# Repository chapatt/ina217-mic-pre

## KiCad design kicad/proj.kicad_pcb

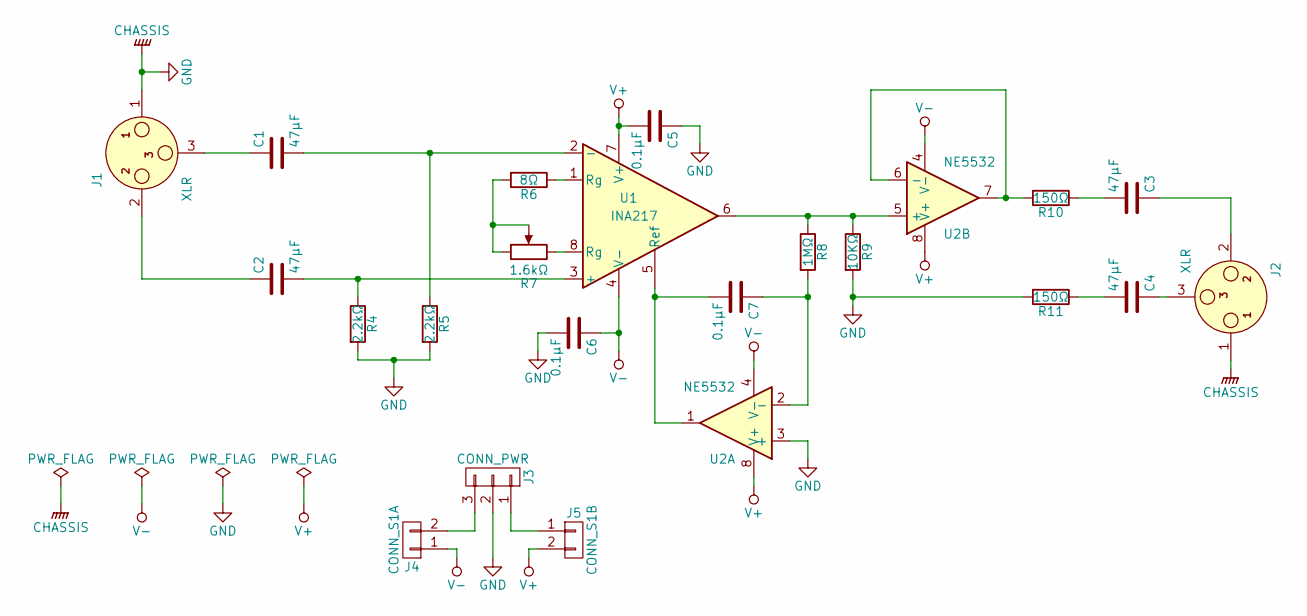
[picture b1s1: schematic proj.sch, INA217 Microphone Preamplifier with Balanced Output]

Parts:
C1, C2, C3, C4: 47μF; CP_Radial_D10.0mm_P5.00mm
C5, C6, C7: 0.1μF; C_Rect_L10.3mm_W5.7mm_P7.50mm_MKS4
J1, J2: XLR; Pin_Header_Straight_1x03_Pitch2.54mm
J3: CONN_PWR; Pin_Header_Straight_1x03_Pitch2.54mm
J4: CONN_S1A; Pin_Header_Straight_1x02_Pitch2.54mm
J5: CONN_S1B; Pin_Header_Straight_1x02_Pitch2.54mm
R4, R5: 2.2kΩ; R_Axial_DIN0207_L6.3mm_D2.5mm_P10.16mm_Horizontal
R6: 8Ω; R_Axial_DIN0207_L6.3mm_D2.5mm_P10.16mm_Horizontal
R7: 1.6kΩ; Pin_Header_Straight_1x03_Pitch2.54mm
R8: 1MΩ; R_Axial_DIN0207_L6.3mm_D2.5mm_P10.16mm_Horizontal
R9: 10KΩ; R_Axial_DIN0207_L6.3mm_D2.5mm_P10.16mm_Horizontal
R10, R11: 150Ω; R_Axial_DIN0207_L6.3mm_D2.5mm_P10.16mm_Horizontal
U1: INA217; DIP-8_W7.62mm
U2: NE5532; DIP-8_W7.62mm

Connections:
GND: C5.1, C6.2, J1.1, J2.1, J3.2, R4.2, R5.2, R9.2, R11.2, U2.3 (+)
unnamed: C1.1, J1.3
unnamed: C1.2, R5.1, U1.2 (-)
unnamed: C2.1, J1.2
unnamed: C2.2, R4.1, U1.3 (+)
unnamed: C3.1, J2.2
unnamed: C3.2, R10.1
unnamed: C4.1, J2.3
unnamed: C4.2, R11.1
unnamed: C7.1, R8.2, U2.2 (-)
unnamed: C7.2, U1.5 (Ref), U2.1
unnamed: J3.1, J5.1
unnamed: J3.3, J4.2
unnamed: R6.1, U1.1 (Rg)
unnamed: R6.2, R7.1, R7.2
unnamed: R7.3, U1.8 (Rg)
unnamed: R8.1, R9.1, U1.6, U2.5 (+)
unnamed: R10.2, U2.6 (-), U2.7
V+: C5.2, J5.2, U1.7 (V+), U2.8 (V+)
V-: C6.1, J4.1, U1.4 (V-), U2.4 (V-)

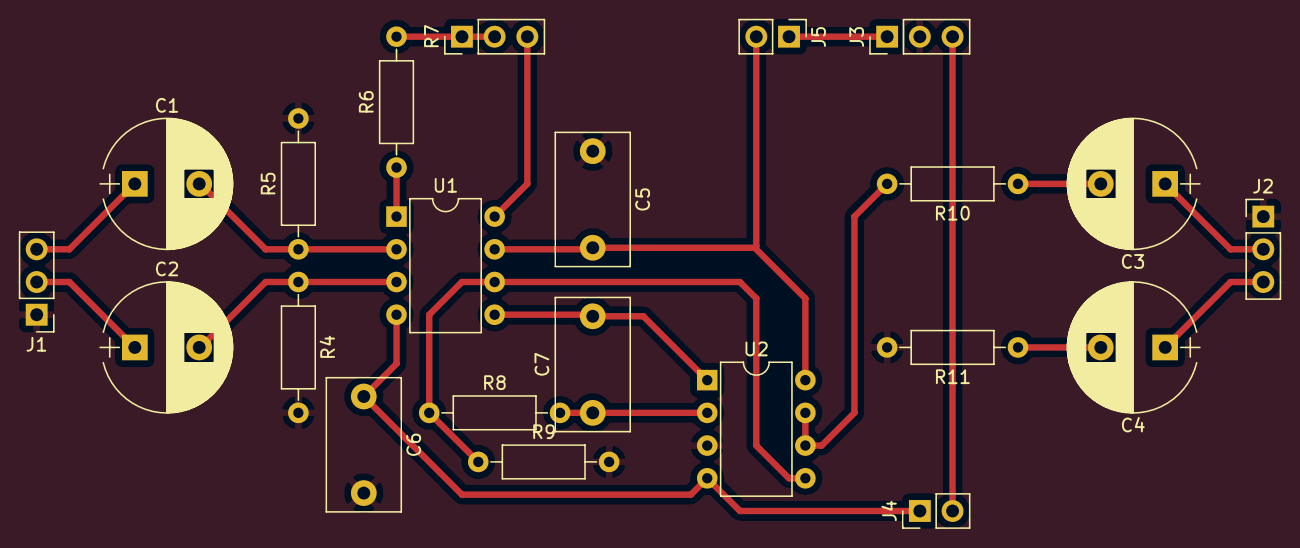
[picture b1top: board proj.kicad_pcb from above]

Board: 2 copper layers, 22 parts (0 on the bottom side), 20 nets.

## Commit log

2017-06-23 Add PDF and PNG exports
2017-06-29 Change C1-4 to non-polar and connected XLR pin 1s to chassis, only GND at input
2017-11-01 Add enclosure
